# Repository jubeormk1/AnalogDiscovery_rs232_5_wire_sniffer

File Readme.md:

# Analog Discovery RS-232 five wire sniffer add on circuit
## Motivation
While troubleshooting an old but extremely robust threadmill, I came across an RS-232 data link between the device and its master computer. Since I do not have any instruments to sniff the messages flowing through a RS-232 link, I decided to build an extension board to add this capability to my Analog Discovery II instrument (AD). To give myself more flexibility, I am adding plenty of headers to monitor extra signal lines in addition to the main RxD and TxD. A total of five lines can be monitored at any time.

## Warnings
Use it at your own risk. I take no responsibility for any damage caused to any device attached to this board. Since this is an experimental circuit, I assume that whoever is reading this is a tinker and has basic skills dealing with extra-low-voltage circuits.

## Features
* Uses the [Texas Instrument TRSF3243EIPWR Multichannel RS-232 compatible line driver/receiver](https://www.ti.com/product/TRSF3243E)
* Five channel RS-232 sniffer
* Passthrough DB9 Male to DB9 female
* RxD and TxD lines always connected to AD instrument ``DIO[0:1]``
* Selectable signals can be connected to the AD ``DIO[2:4]`` via header shunt pins
* RxD and TxD signals connected to AD instrument oscilloscope channels
* Optionally, RxD and TxD can be driven by an AD instrument using ``DIO[8:9]``
* It is also possible to select one more signal line to be driven by an AD instrument ``DIO[10]``
* The driver power can be enable(disable) driving the ``DIO[15]`` high(low)

## Required equipment:
* A data link with RS-232 communication to sniff on
* Personal Computer
* Digilent Analog Discovery (R) Instrument
* Software Digilent Waveforms(R)
* Some extra db9 terminated cables to make the connections

## License

Analog Discovery (R) and Waveforms(R) are Digilent trademarks.
The license is described in the file 'LICENSE'.

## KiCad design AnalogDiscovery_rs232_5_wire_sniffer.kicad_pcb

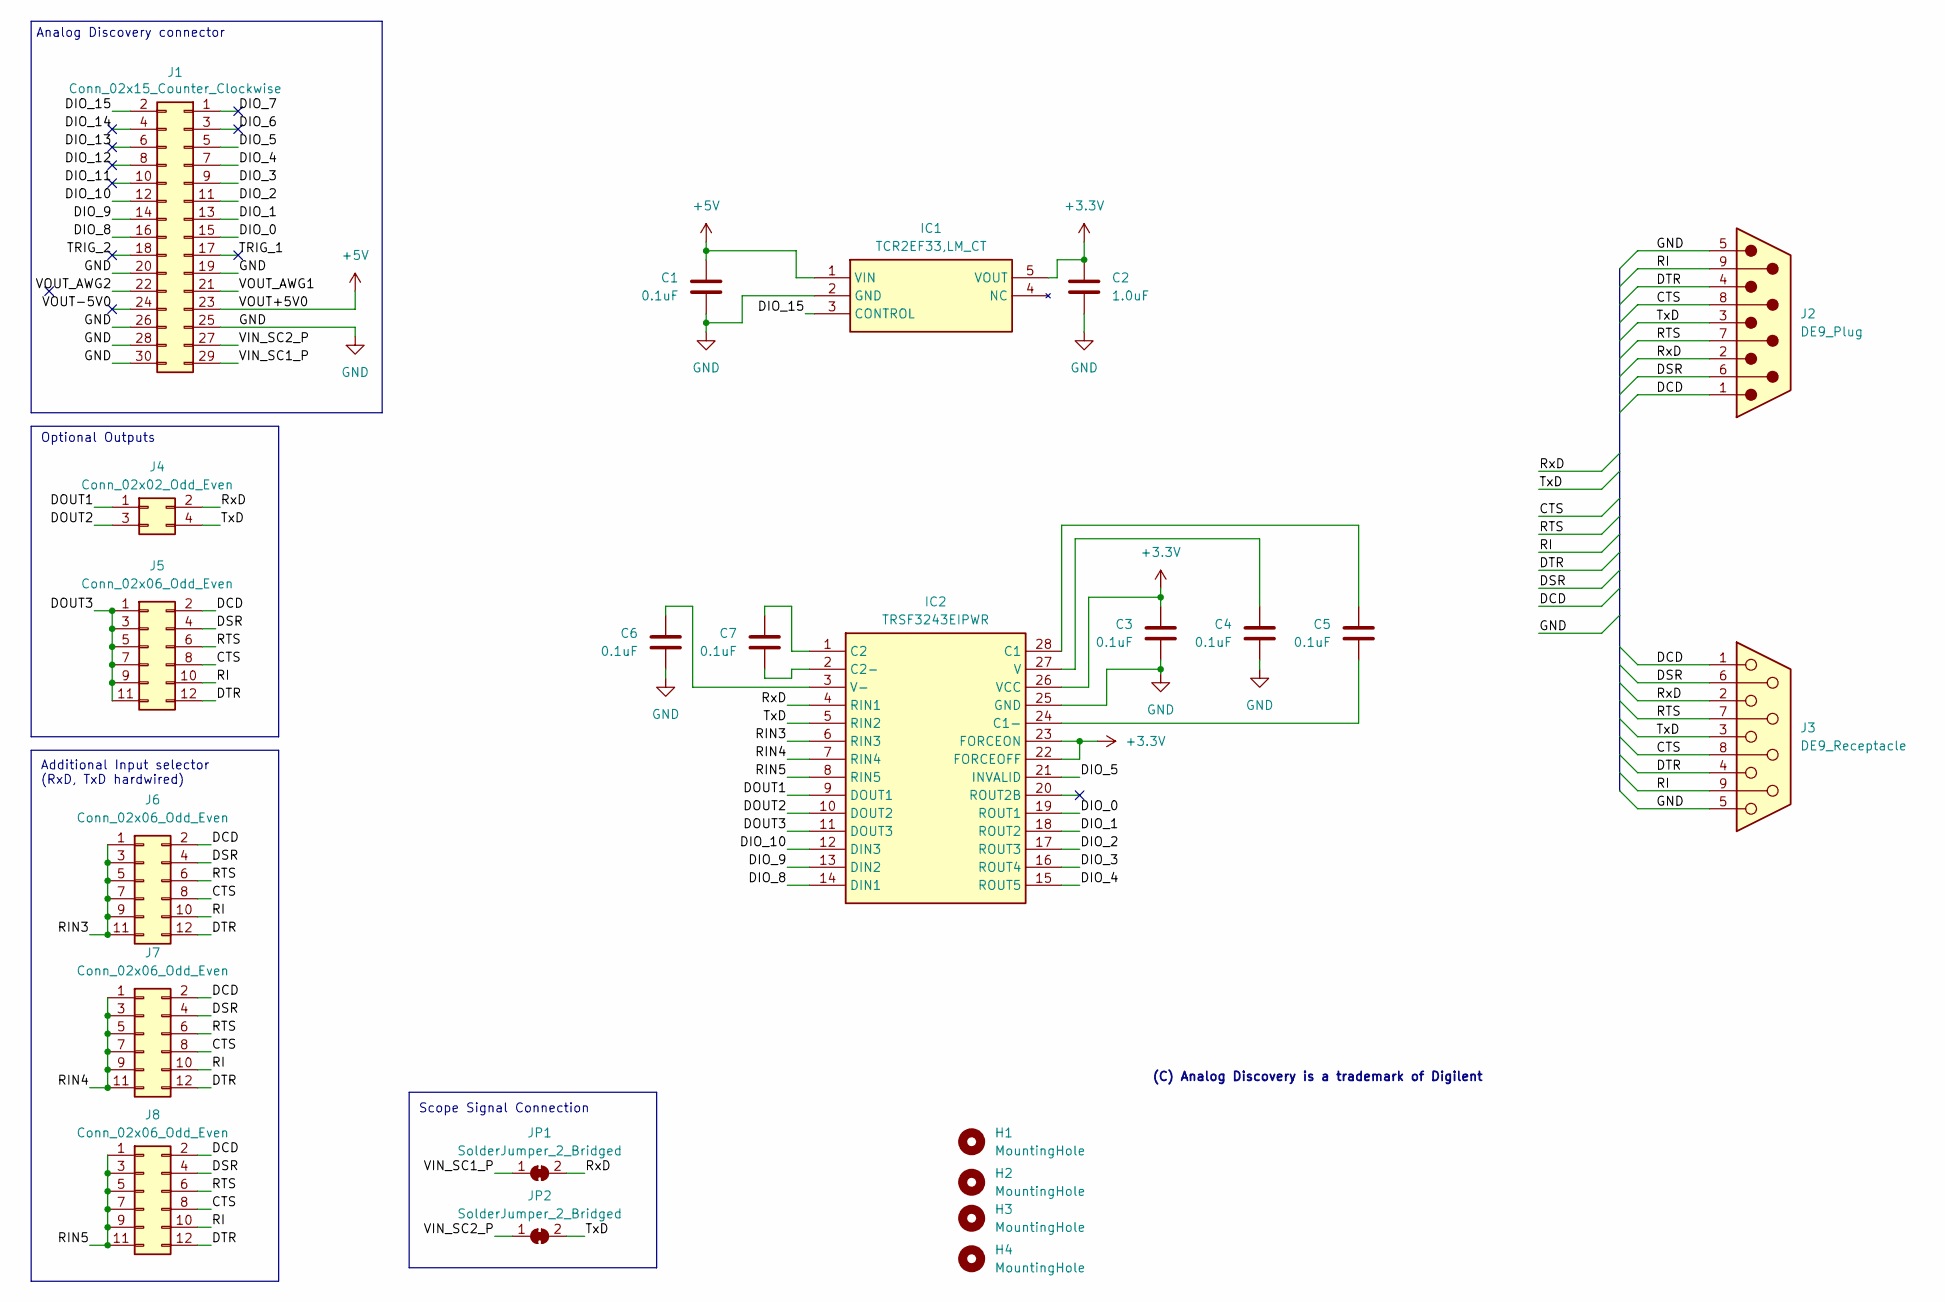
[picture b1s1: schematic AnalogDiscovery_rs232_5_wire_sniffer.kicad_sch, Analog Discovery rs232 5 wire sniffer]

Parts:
C1, C3, C4, C5, C6, C7: 0.1uF; C_0402_1005Metric_Pad0.74x0.62mm_HandSolder; Manufacturer_Part_Number KGM05AR71C103KH
C2: 1.0uF; C_0603_1608Metric_Pad1.08x0.95mm_HandSolder; Manufacturer_Part_Number KGM05AR71C104KH
H1, H2, H3, H4: MountingHole; MountingHole_3.2mm_M3
IC1: TCR2EF33,LM_CT; SOT-23-5_HandSoldering; Manufacturer_Part_Number TCR2EF33,LM(CT; Mouser Part Number 757-TCR2EF33LMCT
IC2: TRSF3243EIPWR; SOP65P640X120-28N; Manufacturer_Part_Number TRSF3243EIPWR; Mouser Part Number 595-TRSF3243EIPWR
J1: Conn_02x15_Counter_Clockwise; PinSocket_2x15_P2.54mm_Horizontal
J2: DE9_Plug; DSUB-9_Female_EdgeMount_P2.77mm
J3: DE9_Receptacle; DSUB-9_Male_EdgeMount_P2.77mm
J4: Conn_02x02_Odd_Even; PinHeader_2x02_P2.54mm_Vertical_SMD
J5, J6, J7, J8: Conn_02x06_Odd_Even; PinHeader_2x06_P2.54mm_Vertical_SMD
JP1, JP2: SolderJumper_2_Bridged; SolderJumper-2_P1.3mm_Bridged_RoundedPad1.0x1.5mm

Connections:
+3.3V: C2.1, C3.2, IC1.5 (VOUT), IC2.22 (FORCEOFF), IC2.23 (FORCEON), IC2.26 (VCC)
+5V: C1.2, IC1.1 (VIN), J1.23
/CTS: J2.8, J3.8, J5.8, J6.8, J7.8, J8.8
/DCD: J2.1, J3.1, J5.2, J6.2, J7.2, J8.2
/DIO_0: IC2.19 (ROUT1), J1.15
/DIO_1: IC2.18 (ROUT2), J1.13
/DIO_2: IC2.17 (ROUT3), J1.11
/DIO_3: IC2.16 (ROUT4), J1.9
/DIO_4: IC2.15 (ROUT5), J1.7
/DIO_5: IC2.21 (INVALID), J1.5
/DIO_6: J1.3
/DIO_7: J1.1
/DIO_8: IC2.14 (DIN1), J1.16
/DIO_9: IC2.13 (DIN2), J1.14
/DIO_10: IC2.12 (DIN3), J1.12
/DIO_11: J1.10
/DIO_12: J1.8
/DIO_13: J1.6
/DIO_14: J1.4
/DIO_15: IC1.3 (CONTROL), J1.2
/DOUT1: IC2.9 (DOUT1), J4.1
/DOUT2: IC2.10 (DOUT2), J4.3
/DOUT3: IC2.11 (DOUT3), J5.1, J5.3, J5.5, J5.7, J5.9, J5.11
/DSR: J2.6, J3.6, J5.4, J6.4, J7.4, J8.4
/DTR: J2.4, J3.4, J5.12, J6.12, J7.12, J8.12
/RI: J2.9, J3.9, J5.10, J6.10, J7.10, J8.10
/RIN3: IC2.6 (RIN3), J6.1, J6.3, J6.5, J6.7, J6.9, J6.11
/RIN4: IC2.7 (RIN4), J7.1, J7.3, J7.5, J7.7, J7.9, J7.11
/RIN5: IC2.8 (RIN5), J8.1, J8.3, J8.5, J8.7, J8.9, J8.11
/RTS: J2.7, J3.7, J5.6, J6.6, J7.6, J8.6
/RxD: IC2.4 (RIN1), J2.2, J3.2, J4.2, JP1.2 (B)
/TRIG_1: J1.17
/TRIG_2: J1.18
/TxD: IC2.5 (RIN2), J2.3, J3.3, J4.4, JP2.2 (B)
/VIN_SC1_P: J1.29, JP1.1 (A)
/VIN_SC2_P: J1.27, JP2.1 (A)
/VOUT-5V0: J1.24
/VOUT_AWG1: J1.21
/VOUT_AWG2: J1.22
GND: C1.1, C2.2, C3.1, C4.1, C6.1, IC1.2 (GND), IC2.25 (GND), J1.19, J1.20, J1.25, J1.26, J1.28, J1.30, J2.5, J3.5
unnamed: C5.2, IC2.28 (C1)
unnamed: C5.1, IC2.24 (C1-)
unnamed: C7.2, IC2.1 (C2)
unnamed: C7.1, IC2.2 (C2-)
unnamed: C4.2, IC2.27 (V)
unnamed: C6.2, IC2.3 (V-)

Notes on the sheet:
Scope Signal Connection
Analog Discovery connector
Optional Outputs
Additional Input selector (RxD, TxD hardwired)
(C) Analog Discovery is a trademark of Digilent

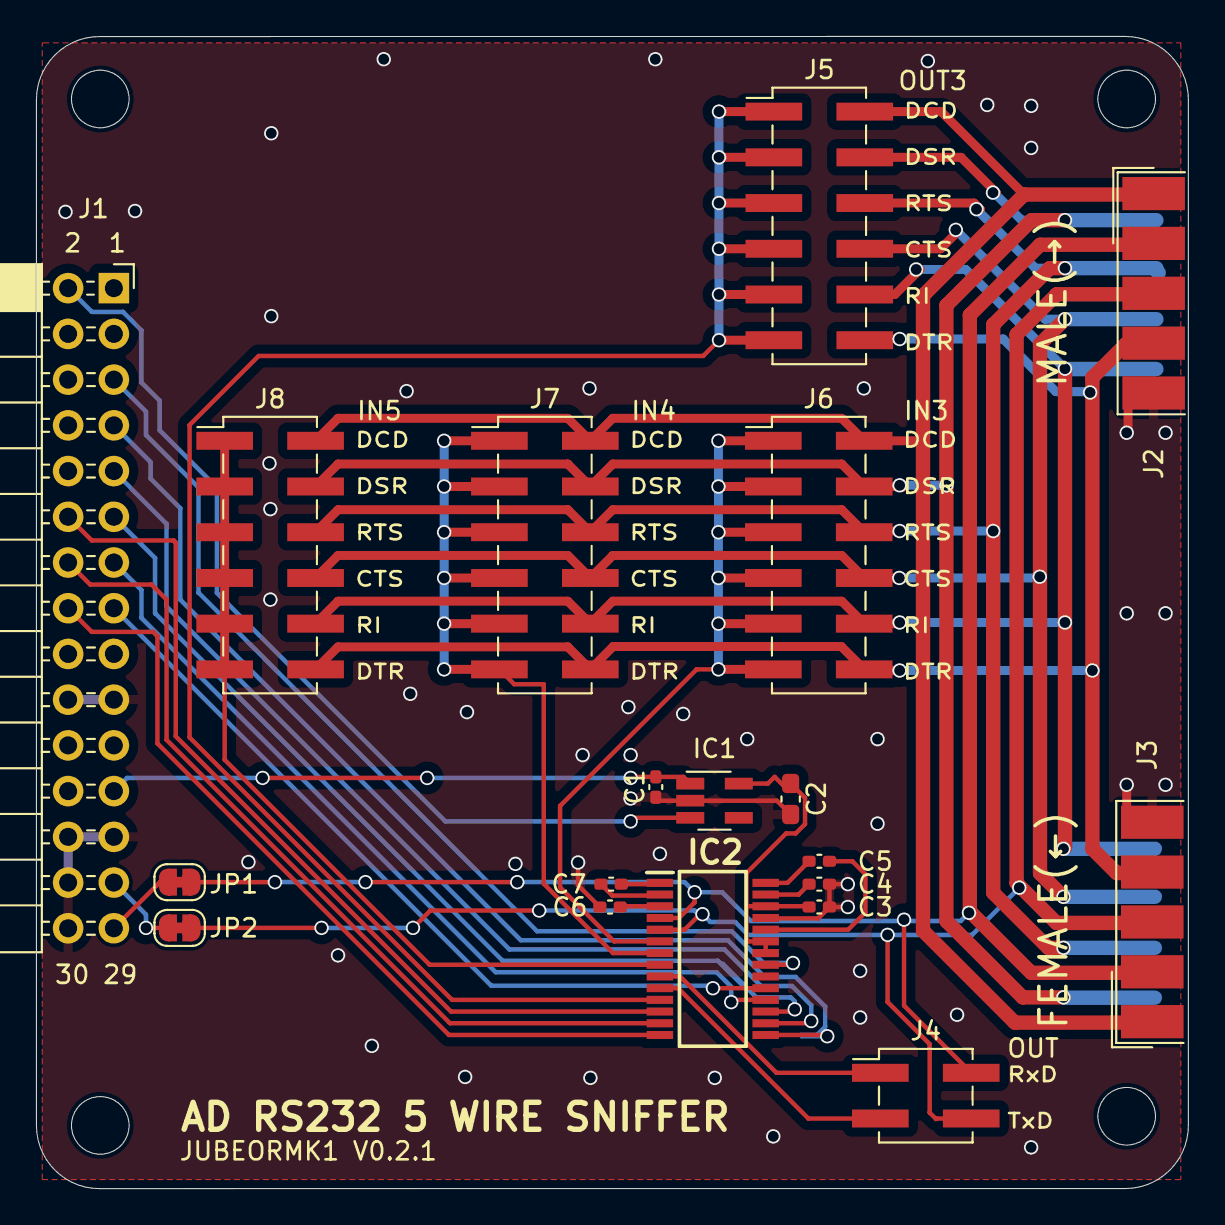
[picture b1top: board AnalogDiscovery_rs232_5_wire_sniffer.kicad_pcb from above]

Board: 2 copper layers, 64.0 x 64.0 mm, 23 parts (0 on the bottom side), 35 nets.

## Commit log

2023-10-01 first upload V0.1
2023-10-01 rm
    Unnecessary
2023-10-01 cropped board render
2023-10-01 Update Readme.md
    Adding a quick board render.
2023-10-01 V0.2
    Silkscreen changes
2023-10-26 Added DigiKey part list
2023-10-29 New revision V0.2.1
    Small changes:
    - Rounded board edges
    - better annotation
    - C2 is 0603 instead of 0402
    - Missing tracks have been removed in J5
